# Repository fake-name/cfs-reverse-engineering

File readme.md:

Creality CFS Filament system Reverse Engineering

This is part of an effort to use the Creality CFS feeder system as a general AMS system for any Klipper-based printer.

This *should* be trivial, as the printer this normally interoperates with is also a Klipper-based machine. However, as usual, Creality are violating the GPL by not releasing their changes and additions to klipper (Creality implemented a custom bus type, and a bunch of utility bits to talk to the filament box).

Given that, the other option is reverse engineering how the feeder works. Fortunately, that should be pretty straightforward for most of the bits.

Anyways, high resolution board images are [here](PCBs.md).

Some attempts at analyzing the various binary firmware and python objects are [here](firmware.md)

Overall system structure:

The board can be flashed with klipper by just treating it as having a STM32F106VET6 (which is binary compatible with the GD32F303VET6). You loose a bit of potential clock-rate by not doing giga-device specific stuff, but this is fairly slow anyways so it should be fine. 

Specifying the klipper host connection to be on PA2/PA3 even works (albeit with RS485).

Current plan to convert the system to klipper in a neat way involves a simple interposer board to re-purpose the RS-485 lines:

The adapter board sits between the existing rear-panel connector and the existing controller board. It basically has 3 connectors, a CAN transciever, and a bypass capacitors. It simply carries all other signals + power through the PCB, but replaces the two RS-485 lines with CAN signalling. 

Since the IO needed to drive a CAN interface is exposed on the unused "J10" connector, that is connected to an appropriate CAN bus transciever IC (a [TCAN332G](https://www.ti.com/lit/ds/symlink/tcan332g.pdf)). 

The other end is another custom PCB. In this case, it's another custom PCB heavily inspired by the [candleLight FD](https://linux-automation.com/en/products/candlelight-fd.html) (read: I used some of their schematics for a starting point, the entire layout is my own work). It breaks out the CFS bus to a usb-CAN adapter (via [candleLight_fw](https://github.com/candle-usb/candleLight_fw) and the 24V power in via either a DC Barrel jack or a 2-pin micro-fit connector (there are pads for both on the PCB).

It also has a pair of LEDs to indicate buffer status, and some activity LEDs. 

Both boards are up at [Adapter](~/Adapter/). License for them is GPL3, since the candleLight FD is GPL3.

I had JLCPCB do the PCBs, they work out to ~$7 ea (CAN Adapter) and ~$10 ea (CFS-Bus Adapter), at qty 5 of each. I'm also trying LCSC's [custom-cable service](https://www.lcsc.com/customcables?utm_source=customcables&utm_medium=navbar) to make the short interposing cables, which wound up being ~$50 for 10 of each.

Full production files for each of the PCBs are in the respective folders, they should drag & drop into JLCPCB's PCBA service. The cables are based on a lot of guesswork about what the right connectors are, once I confirm I have the right part-numbers, I'll document that here as well.

Note that immediately after ordering the CFS-Bus-Adapter, I realized it would be super neat to allow the CAN transciever to be either connected to the CAN peripheral in the MCU (which is how it is now), and a UART interface. That would let this interact with the existing firmware if/when it get's properly reverse engineered, or Creality finally stops violating the GPL and provides the source for their [distributed-in-compiled-form-only klipper extensions](https://github.com/Guilouz/Creality-K2Plus-Extracted-Firmwares/tree/main/Firmware/usr/share/klipper/klippy/extras) (see all `.so` files, which are compiled with cython to make them opaque).

------

First rev board issues:

 - Pinout on J3 for CFS Can adapter board is reversed.   
   This can be fixed by just mirroring the routing of the jumper cable.
 - The open-collector buffer signals have pullups to 5V in the buffer. That means the buffer status LED resistors as implemented (i.e. between 24V and the buffer status pins) are effectively always on, since the 5V pullup winds up sinking current from the 24V LED rail.   
   This needs to be fixed by rev-ing the board (or with track hackery). Right now, the CFS buffer just changes the LED brightness, rather then turning them on and off.

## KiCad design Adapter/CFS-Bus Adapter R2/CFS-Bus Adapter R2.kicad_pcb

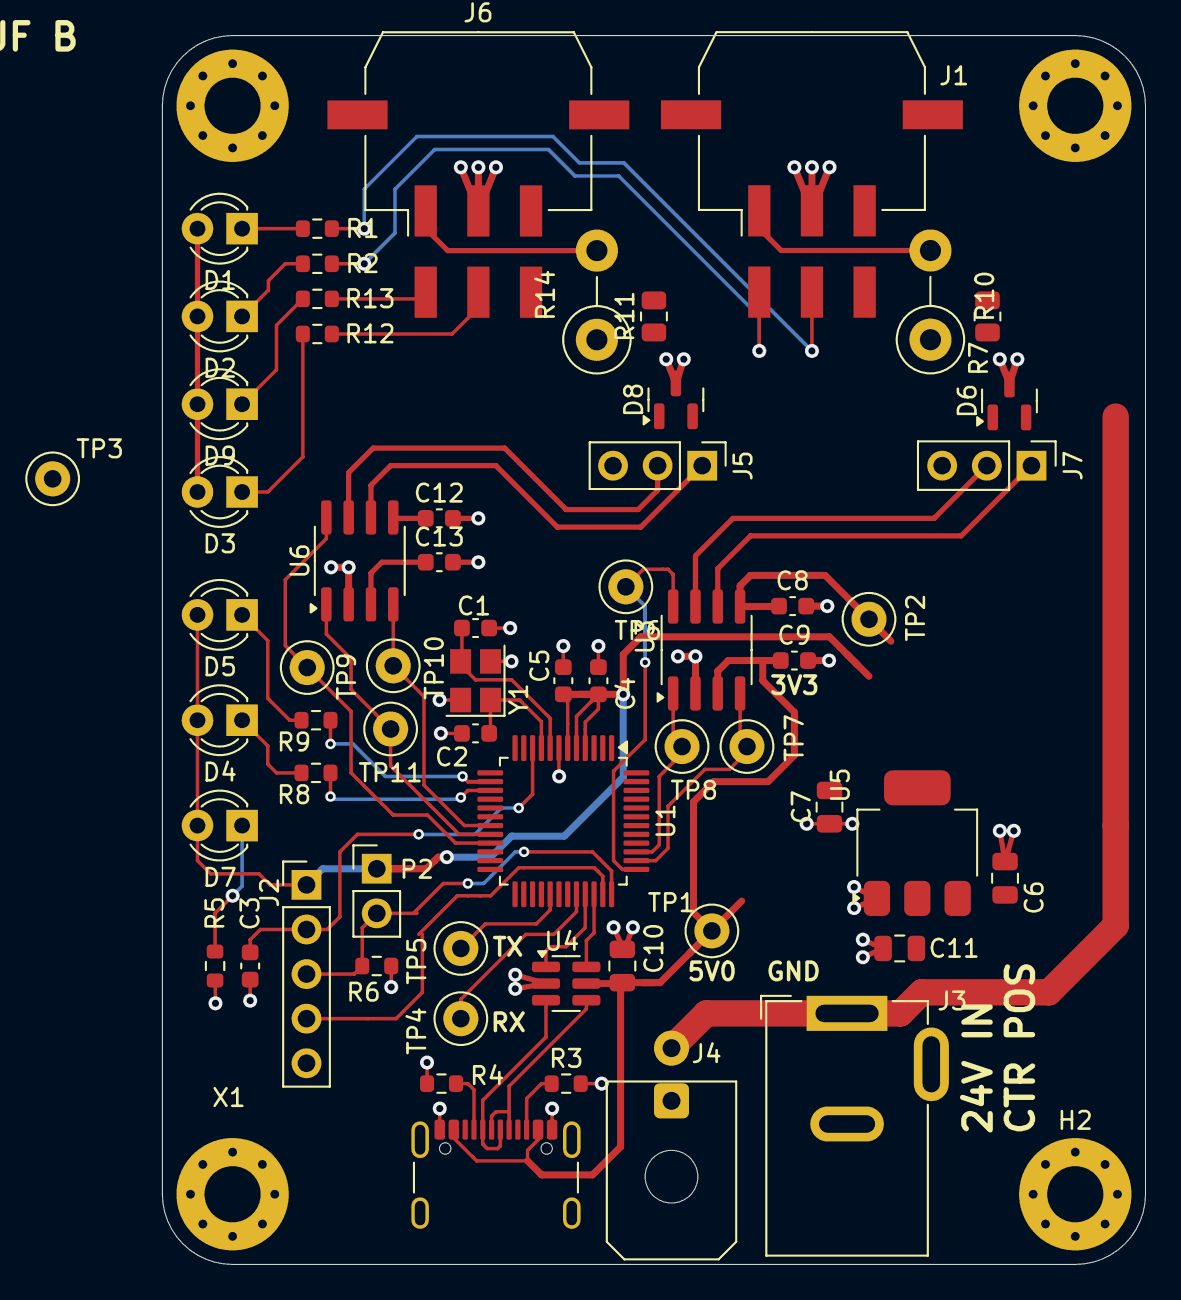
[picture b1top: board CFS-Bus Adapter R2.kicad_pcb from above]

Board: 2 copper layers, 56.0 x 70.0 mm, 66 parts (0 on the bottom side), 40 nets.

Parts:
C1, C2: 6p2_0603_C0G_5%_50V_-40C..125C_Chip-Capacitor; C_0603_1608Metric
C3, C4, C5: 100n; C_0603_1608Metric
C6, C7, C10, C11: 10u_0805_X7R_10%_10V_-40C..125C_Chip-Capacitor; C_0805_2012Metric
C8, C9, C12, C13: 100n_0603_X7R_10%_50V_-40C..125C_Chip-Capacitor; C_0603_1608Metric
D1, D2, D3, D4, D5, D7, D9: LED; LED_D3.0mm
D6, D8: NUP2105L; SOT-23
H1, H2, H3, H4: MountingHole; MountingHole_3.2mm_M3_Pad_Via
J1, J6: Conn_02x03_Top_Bottom; Molex_Micro-Fit_3.0_43045-0610_2x03-1MP_P3.00mm_Horizontal
J2: Conn_01x05; PinHeader_1x05_P2.54mm_Vertical
J3: Barrel_Jack_Switch_MountingPin; BarrelJack_GCT_DCJ200-10-A_Horizontal
J4: Conn_01x02; Molex_Micro-Fit_3.0_43045-0200_2x01_P3.00mm_Horizontal
J5, J7: Conn_01x03; PinHeader_1x03_P2.54mm_Vertical
P2: CONN_01X02; PinHeader_1x02_P2.54mm_Vertical
R1, R2, R12, R13: 5k1; R_0603_1608Metric
R3, R4: 5k1_0603_100mW_1%_E24_Chip-Resistor; R_0603_1608Metric
R5, R8, R9: 1k_0603_100mW_1%_E24_Chip-Resistor; R_0603_1608Metric
R6: 10k_0603_100mW_1%_E24_Chip-Resistor; R_0603_1608Metric
R7, R11: 120R_0805_125mW_1%_E24_Chip-Resistor; R_0805_2012Metric
R10, R14: 120R_0805_125mW_1%_E24_Chip-Resistor; R_Axial_DIN0411_L9.9mm_D3.6mm_P5.08mm_Vertical
TP1, TP2, TP3: TP2.0mm; TestPoint_Loop_D1.80mm_Drill1.0mm_Beaded
TP4, TP5: TP1.0mm; TestPoint_Loop_D1.80mm_Drill1.0mm_Beaded
TP6, TP7, TP8, TP9, TP10, TP11: TestPoint; TestPoint_Loop_D1.80mm_Drill1.0mm_Beaded
U1: STM32G0B1CBT; LQFP-48_7x7mm_P0.5mm
U3, U6: TJA1051T3; SOIC-8_3.9x4.9mm_P1.27mm
U4: IP4234CZ6; SC-74-6_1.55x2.9mm_P0.95mm
U5: AMS1117-3.3; SOT-223-3_TabPin2
X1: 629722000214_pasteInHole; USB_C_Receptacle_GCT_USB4105-xx-A_16P_TopMnt_Horizontal
Y1: 830108313809; Crystal_SMD_3225-4Pin_3.2x2.5mm

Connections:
+3V3: C4.1, C5.1, C7.1, C8.1, C11.1, C12.1, D4.2 (A), D5.2 (A), D7.2 (A), J2.1, P2.1, TP2.1, U1.4 (VBAT), U1.5 (VREF+), U1.6 (VDD/VDDA), U3.5 (VIO), U5.2 (VO), U6.5 (VIO)
+5V: C6.1, C9.1, C10.1, C13.1, D1.2 (A), D2.2 (A), D3.2 (A), D9.2 (A), TP1.1, U3.3 (VCC), U4.5 (VP), U5.3 (VI), U6.3 (VCC), X1.A4 (VBUS), X1.A9 (VBUS), X1.B4 (VBUS), X1.B9 (VBUS)
+24V: J1.3, J3.1, J4.2, J6.3
/MCU/CAN1_RX: TP7.1, U1.38 (PD0), U3.4 (RXD)
/MCU/CAN1_S: TP6.1, U1.37 (PA15), U3.8 (S)
/MCU/CAN1_TX: TP8.1, U1.39 (PD1), U3.1 (TXD)
/MCU/CAN2_RX: TP10.1, U1.19 (PB0), U6.4 (RXD)
/MCU/CAN2_S: TP9.1, U1.21 (PB2), U6.8 (S)
/MCU/CAN2_TX: TP11.1, U1.20 (PB1), U6.1 (TXD)
/MCU/LED_RX: R9.2, U1.14 (PA3)
/MCU/LED_TX: R8.2, U1.15 (PA4)
/MCU/NRST: C3.1, J2.2, U1.10 (PF2/NRST)
/MCU/RX: TP4.1, U1.32 (PA10)
/MCU/SWCLK: J2.3, P2.2, R6.1, U1.36 (PA14/BOOT0)
/MCU/SWDIO: J2.4, U1.35 (PA13)
/MCU/TX: TP5.1, U1.29 (PA9)
/MCU/USB_{N}: U1.33 (PA11[PA9]), U4.1
/MCU/USB_{P}: U1.34 (PA12[PA10]), U4.6
/RS485-2-A: D8.1 (K), J5.2, J6.6, R11.1, R14.1, U6.7 (CANH)
/RS485-2-B: D8.2 (K), J5.1, J6.1, R11.2, R14.2, U6.6 (CANL)
/RS485-A: D6.1 (K), J1.6, J7.2, R7.1, R10.1, U3.7 (CANH)
/RS485-B: D6.2 (K), J1.1, J7.1, R7.2, R10.2, U3.6 (CANL)
/USB_N: U4.3, X1.A7 (DN1), X1.B7 (DN2)
/USB_P: U4.4, X1.A6 (DP1), X1.B6 (DP2)
GND: C1.1, C2.1, C3.2, C4.2, C5.2, C6.2, C7.2, C8.2, C9.2, C10.2, C11.2, C12.2, C13.2, D6.3 (A), D8.3 (A), J1.2, J2.5, J3.2, J3.3, J4.1, J5.3, J6.2, J7.3, R3.2, R4.2, R5.2, R6.2, TP3.1, U1.7 (VSS/VSSA), U3.2 (GND), U4.2 (VN), U5.1 (GND), U6.2 (GND), X1.A1 (GND), X1.B1 (GND), Y1.2 (GND), Y1.4 (GND)
unnamed: D1.1 (K), R1.1
unnamed: D2.1 (K), R2.1
unnamed: D3.1 (K), R12.1
unnamed: D4.1 (K), R8.1
unnamed: D5.1 (K), R9.1
unnamed: D7.1 (K), R5.1
unnamed: D9.1 (K), R13.1
unnamed: J1.4, R2.2
unnamed: J1.5, R1.2
unnamed: J6.4, R13.2
unnamed: J6.5, R12.2
unnamed: C1.2, U1.8 (PF0/OSC_IN), Y1.3 (C_{2})
unnamed: C2.2, U1.9 (PF1/OSC_OUT), Y1.1 (C_{1})
unnamed: R4.1, X1.A5 (CC1)
unnamed: R3.1, X1.B5 (CC2)

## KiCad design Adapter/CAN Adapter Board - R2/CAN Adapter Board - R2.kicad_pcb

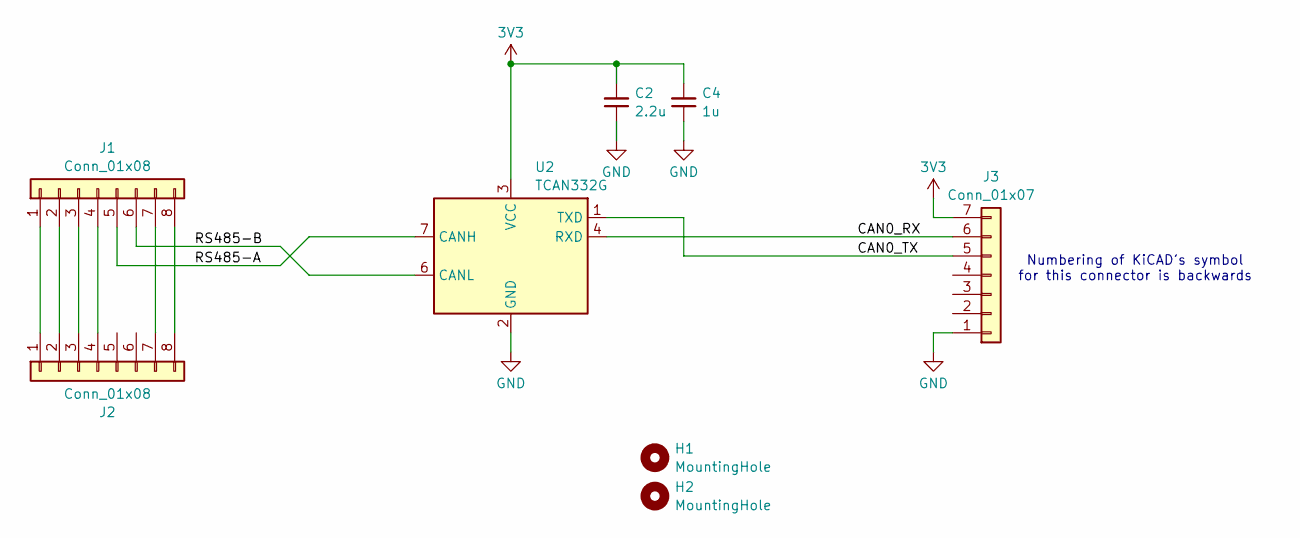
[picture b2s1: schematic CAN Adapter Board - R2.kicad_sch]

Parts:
C2: 2.2u; C_0603_1608Metric
C4: 1u; C_0402_1005Metric
H1, H2: MountingHole; MountingHole_3.2mm_M3_Pad_Via
J1, J2: Conn_01x08; JST_PH_B8B-PH-SM4-TB_1x08-1MP_P2.00mm_Vertical
J3: Conn_01x07; JST_GH_BM07B-GHS-TBT_1x07-1MP_P1.25mm_Vertical
U2: TCAN332G; SOIC-8_3.9x4.9mm_P1.27mm

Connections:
3V3: C2.2, C4.2, J3.7, U2.3 (VCC)
/CAN0_RX: J3.6, U2.4 (RXD)
/CAN0_TX: J3.5, U2.1 (TXD)
/RS485-A: J1.5, U2.7 (CANH)
/RS485-B: J1.6, U2.6 (CANL)
GND: C2.1, C4.1, J3.1, U2.2 (GND)
unnamed: J1.1, J2.1
unnamed: J1.2, J2.2
unnamed: J1.3, J2.3
unnamed: J1.4, J2.4
unnamed: J1.7, J2.7
unnamed: J1.8, J2.8

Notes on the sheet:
Numbering of KiCAD's symbol for this connector is backwards

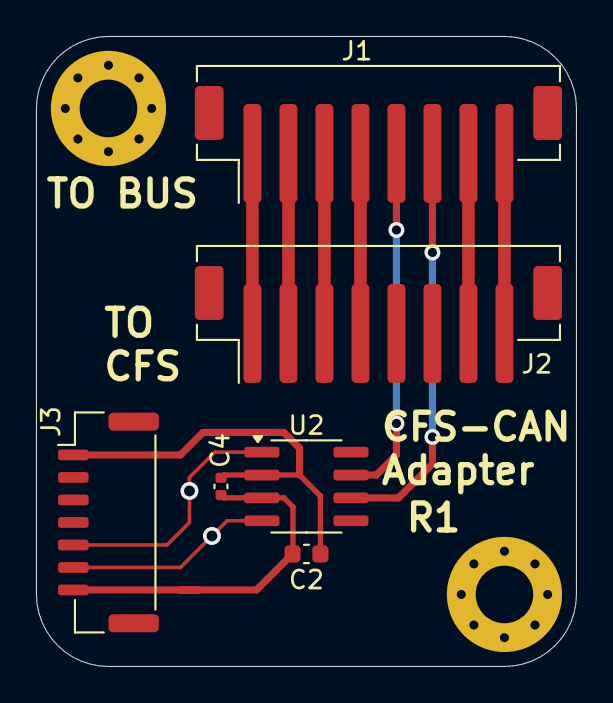
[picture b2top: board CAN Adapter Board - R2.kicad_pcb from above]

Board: 2 copper layers, 30.0 x 35.0 mm, 8 parts (0 on the bottom side), 12 nets.

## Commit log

2025-02-06 Images!
2025-02-06 Add text file stuff.
2025-02-08 Ghidra files for stuff!
2025-02-08 Moar!
2025-02-11 Pinout tables!
2025-02-15 Add another dump image to ghidra. This one has memory segments dumped from the real device.
2025-02-17 Work out logical pins from physical.
2025-02-17 Add logic analyser probes of the external devices so we can do things like see how the LCD and RFID readers are configured.
2025-02-20 Moar.
2025-02-21 Add block diagram.
2025-02-27 More connector lookups.
2025-03-03 Add various adapter boards that I just ordered
2025-03-03 More readme stuff.
2025-03-03 Note board files, and that creality are jerks.
2025-03-03 Path typo
2025-03-19 Add notes on the first board rev.
2025-04-19 Add second-rev of both boards with the issues fixed.
